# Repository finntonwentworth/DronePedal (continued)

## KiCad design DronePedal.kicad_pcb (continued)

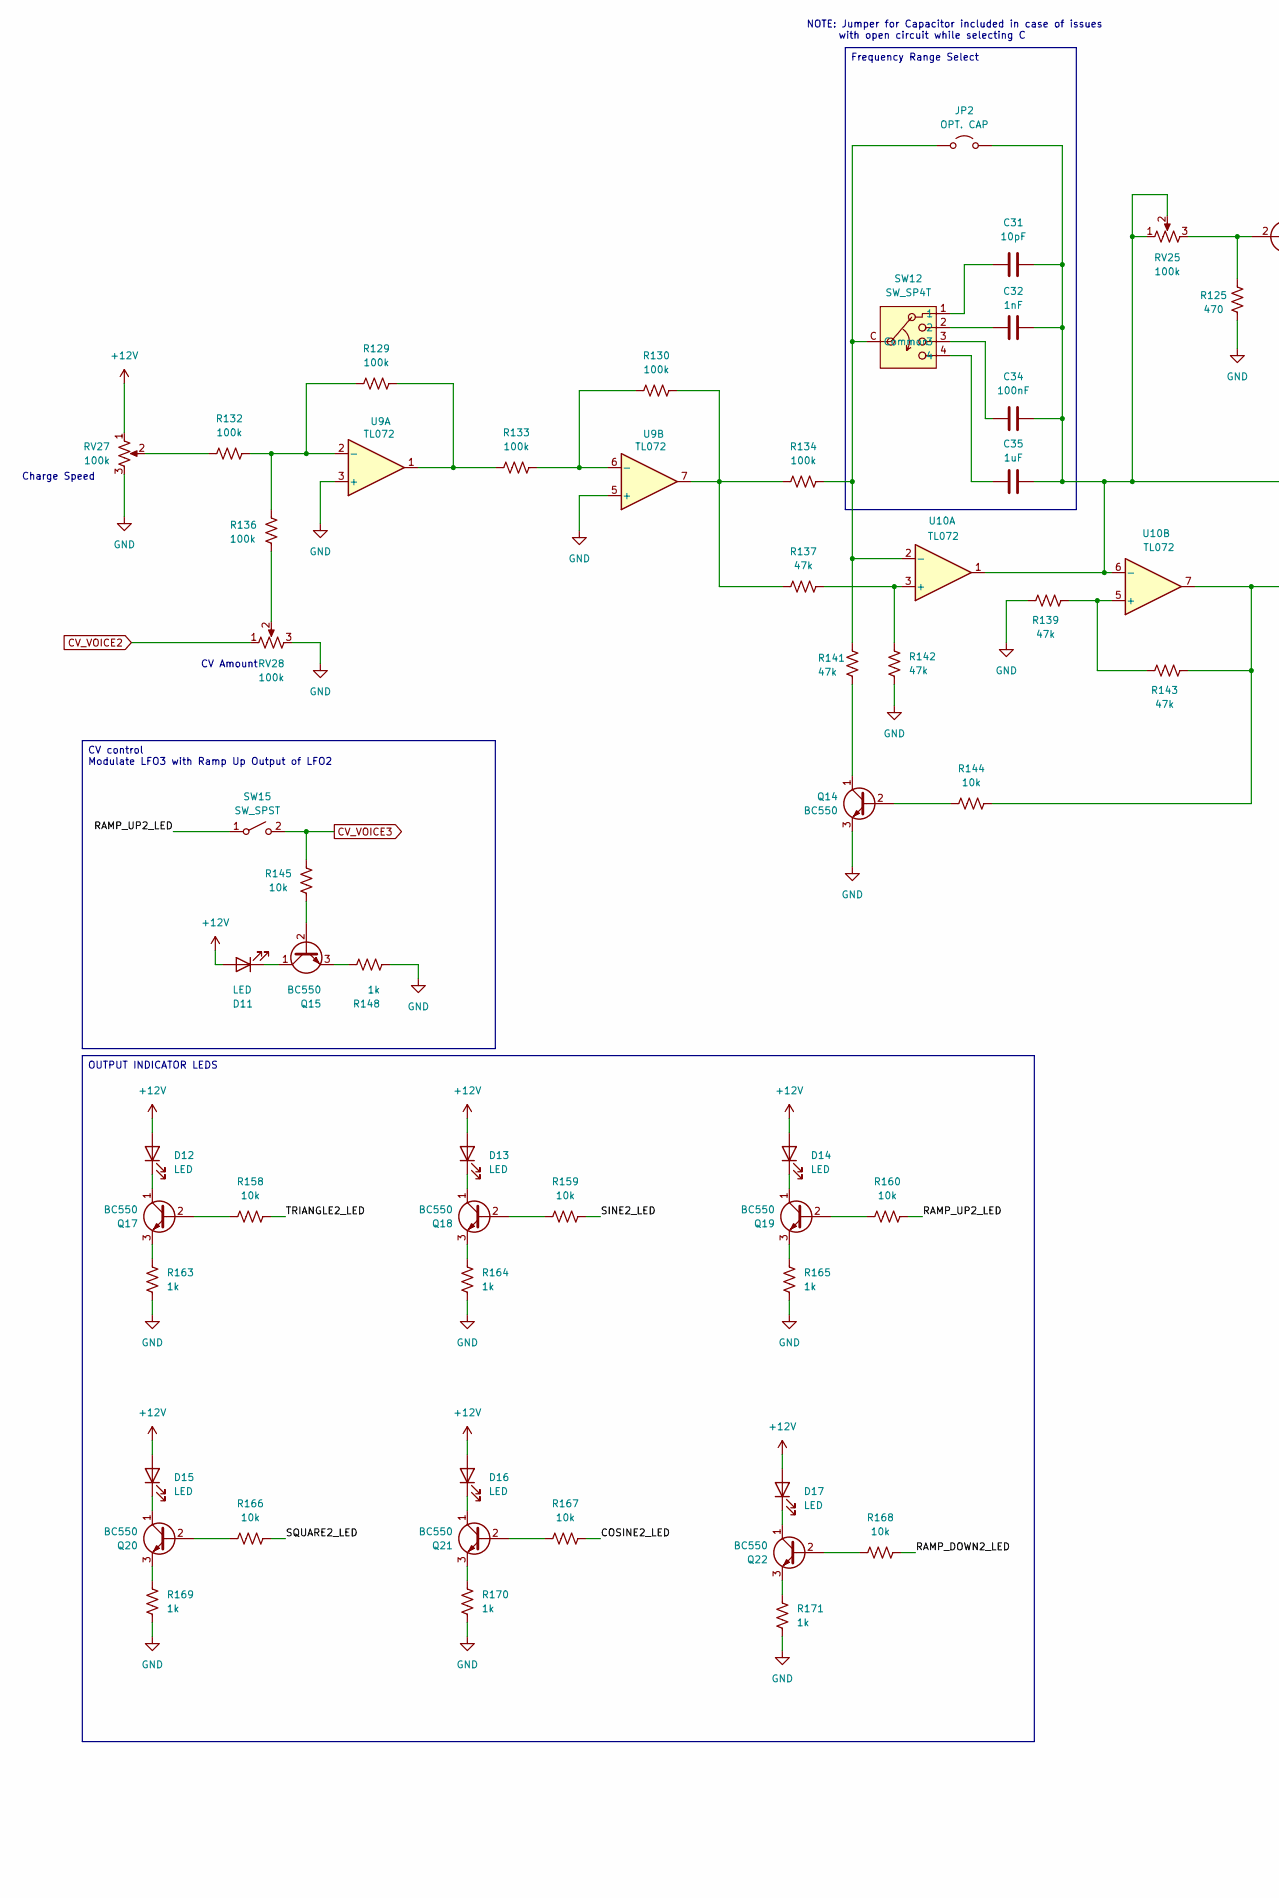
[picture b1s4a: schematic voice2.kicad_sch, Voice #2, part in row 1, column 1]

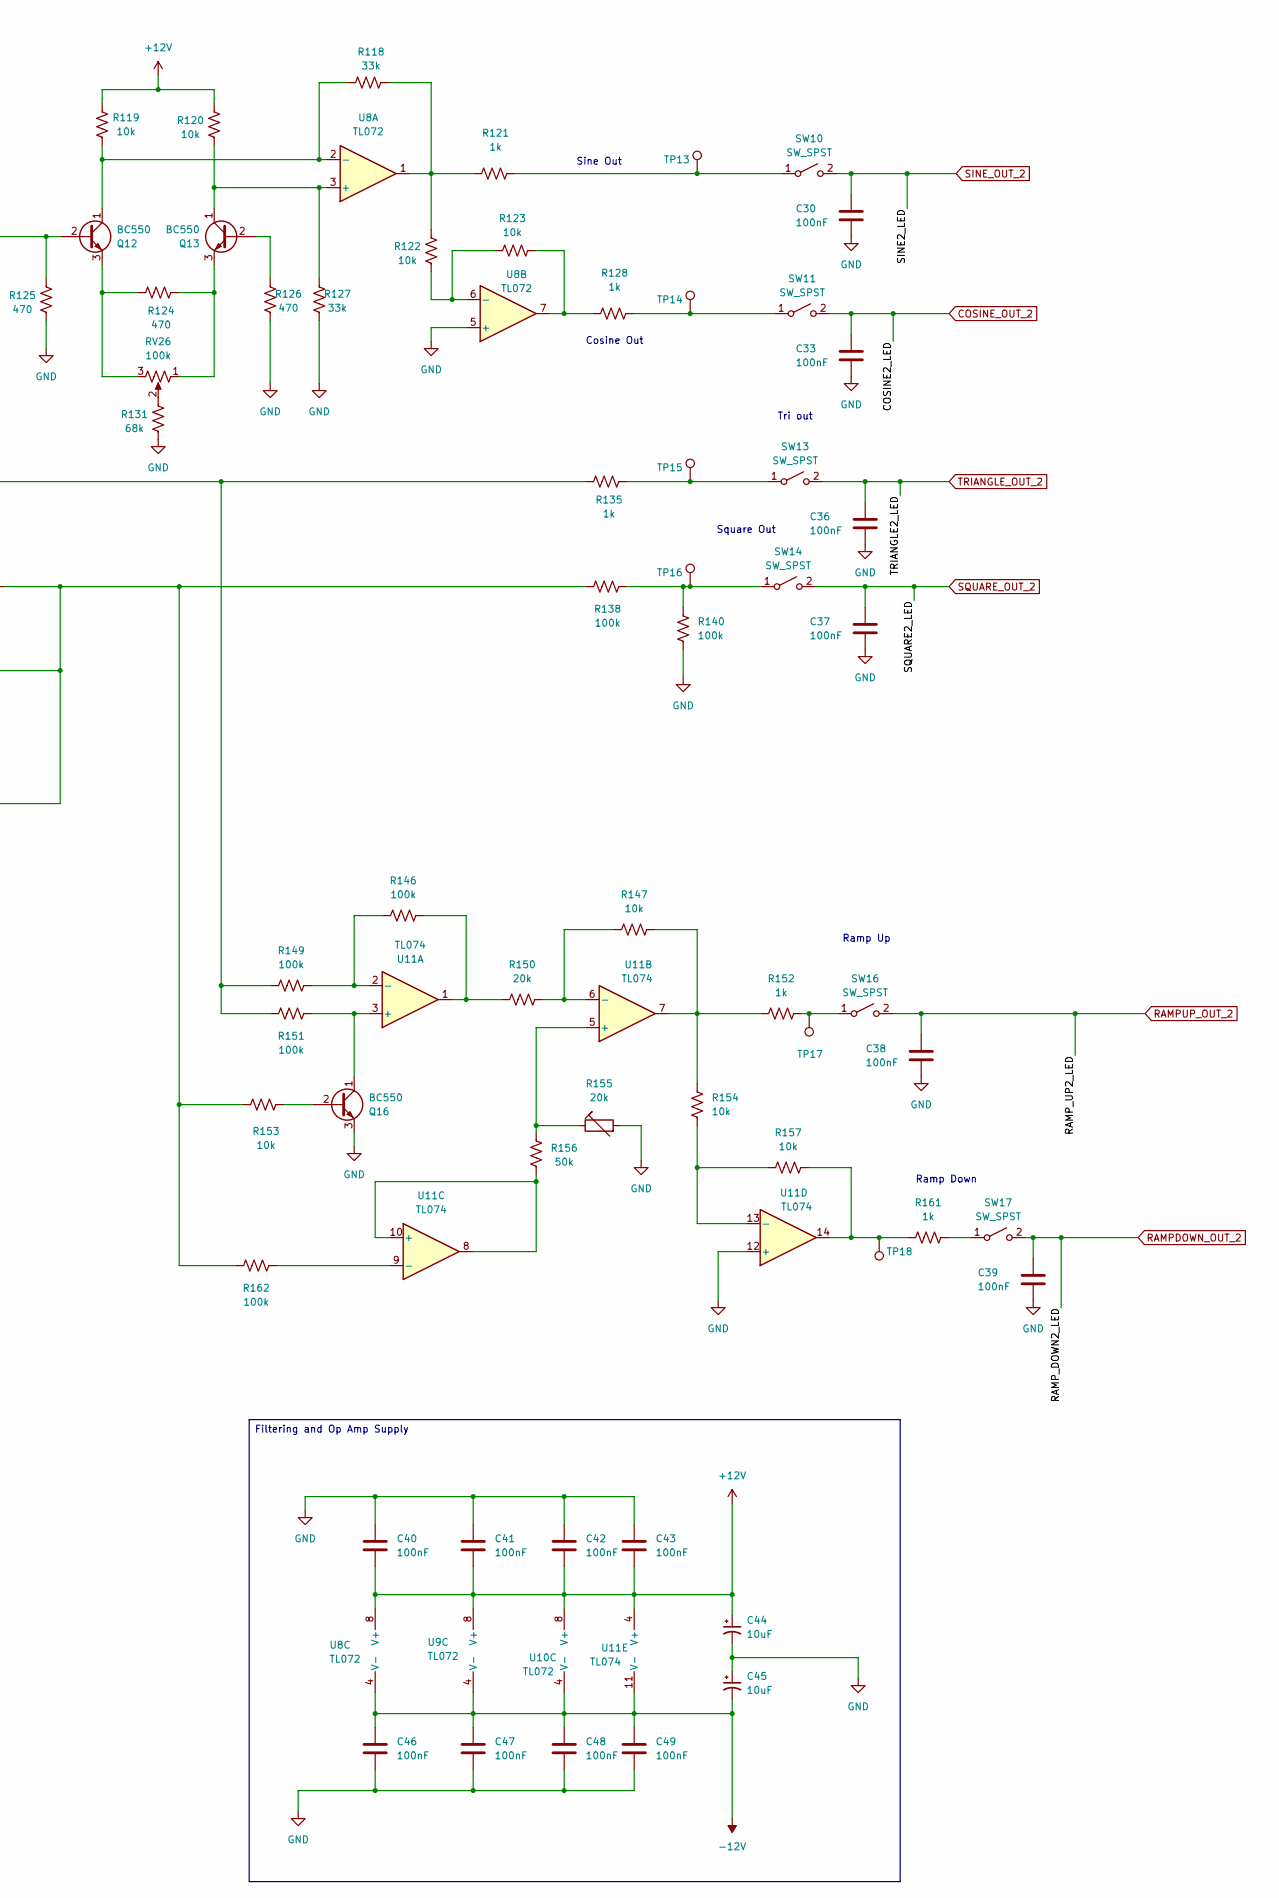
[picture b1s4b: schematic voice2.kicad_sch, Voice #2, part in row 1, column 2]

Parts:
C30, C33, C34, C36, C37, C38, C39, C40, C41, C42, C43, C46, C47, C48, C49: 100nF; C_Disc_D6.0mm_W2.5mm_P5.00mm
C31: 10pF; C_Disc_D4.7mm_W2.5mm_P5.00mm
C32: 1nF; C_Disc_D6.0mm_W2.5mm_P5.00mm
C35: 1uF; C_Disc_D5.0mm_W2.5mm_P2.50mm
C44, C45: 10uF; C_Disc_D6.0mm_W2.5mm_P5.00mm
D11, D12, D13, D14, D15, D16, D17: LED; LED_D1.8mm_W3.3mm_H2.4mm
JP2: OPT. CAP; C_Disc_D5.0mm_W2.5mm_P2.50mm
Q12, Q13, Q14, Q15, Q16, Q17, Q18, Q19, Q20, Q21, Q22: BC550; TO-92_Inline
R118, R127: 33k; R_Axial_DIN0204_L3.6mm_D1.6mm_P5.08mm_Horizontal
R119, R120, R122, R123, R144, R145, R147, R153, R154, R157, R158, R159, R160, R166, R167, R168: 10k; R_Axial_DIN0204_L3.6mm_D1.6mm_P5.08mm_Horizontal
R121, R128, R135, R148, R152, R161, R163, R164, R165, R169, R170, R171: 1k; R_Axial_DIN0204_L3.6mm_D1.6mm_P5.08mm_Horizontal
R124, R125, R126: 470; R_Axial_DIN0204_L3.6mm_D1.6mm_P5.08mm_Horizontal
R129, R130, R132, R133, R134, R136, R138, R140, R146, R149, R151, R162: 100k; R_Axial_DIN0207_L6.3mm_D2.5mm_P10.16mm_Horizontal
R131: 68k; R_Axial_DIN0204_L3.6mm_D1.6mm_P5.08mm_Horizontal
R137, R139, R141, R142, R143: 47k; R_Axial_DIN0204_L3.6mm_D1.6mm_P5.08mm_Horizontal
R150: 20k; R_Axial_DIN0204_L3.6mm_D1.6mm_P5.08mm_Horizontal
R155: 20k; PinHeader_1x03_P2.54mm_Vertical
R156: 50k; R_Axial_DIN0207_L6.3mm_D2.5mm_P7.62mm_Horizontal
RV25, RV26, RV27, RV28: 100k; PinHeader_1x03_P2.54mm_Vertical
SW10, SW11, SW13, SW14, SW15, SW16, SW17: SW_SPST; PinHeader_1x02_P2.54mm_Vertical
SW12: SW_SP4T; PinHeader_1x05_P2.54mm_Vertical
TP13, TP14, TP15, TP16, TP17, TP18: TestPoint_Pad_D1.0mm
U8, U9, U10: TL072; DIP-8_W7.62mm
U11: TL074; DIP-14_W7.62mm

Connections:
+12V: C40.2, C41.2, C42.2, C43.2, C44.1, D11.2 (A), D12.2 (A), D13.2 (A), D14.2 (A), D15.2 (A), D16.2 (A), D17.2 (A), R119.1, R120.1, RV27.1, U8.8 (V+), U9.8 (V+), U10.8 (V+), U11.4 (V+); also elsewhere on the board
-12V: C45.2, C46.1, C47.1, C48.1, C49.1, U8.4 (V-), U9.4 (V-), U10.4 (V-), U11.11 (V-); also elsewhere on the board
COSINE_OUT_2: C33.1, R167.2, SW11.2 (B); also elsewhere on the board
CV_VOICE2: RV28.1; also elsewhere on the board
CV_VOICE3: R145.2, SW15.2 (B); also elsewhere on the board
GND: C30.2, C33.2, C36.2, C37.2, C38.2, C39.2, C40.1, C41.1, C42.1, C43.1, C44.2, C45.1, C46.2, C47.2, C48.2, C49.2, Q14.3 (E), Q16.3 (E), R125.2, R126.1, R127.1, R131.2, R139.2, R140.1, R142.1, R148.1, R155.2, R163.1, R164.1, R165.1, R169.1, R170.1, R171.1, RV27.3, RV28.3, U8.5 (+), U9.3 (+), U9.5 (+), U11.12 (+); also elsewhere on the board
unnamed: C31.1, SW12.1
unnamed: C32.2, SW12.2
unnamed: C34.2, SW12.3
unnamed: C35.2, SW12.4
unnamed: D11.1 (K), Q15.1 (C)
unnamed: D12.1 (K), Q17.1 (C)
unnamed: D13.1 (K), Q18.1 (C)
unnamed: D14.1 (K), Q19.1 (C)
unnamed: D15.1 (K), Q20.1 (C)
unnamed: D16.1 (K), Q21.1 (C)
unnamed: D17.1 (K), Q22.1 (C)
unnamed: JP2.1 (A), R134.2, R141.2, SW12.C (Common), U10.2 (-)
unnamed: C31.2, C32.1, C34.1, C35.1, JP2.2 (B), R135.2, R149.1, R151.1, RV25.1, RV25.2, U10.1, U10.6 (-)
unnamed: Q12.2 (B), R125.1, RV25.3
unnamed: Q12.1 (C), R118.2, R119.2, U8.2 (-)
unnamed: Q12.3 (E), R124.1, RV26.3
unnamed: Q13.2 (B), R126.2
unnamed: Q13.1 (C), R120.2, R127.2, U8.3 (+)
unnamed: Q13.3 (E), R124.2, RV26.1
unnamed: Q14.2 (B), R144.1
unnamed: Q14.1 (C), R141.1
unnamed: Q15.2 (B), R145.1
unnamed: Q15.3 (E), R148.2
unnamed: Q16.2 (B), R153.2
unnamed: Q16.1 (C), R151.2, U11.3 (+)
unnamed: Q17.2 (B), R158.1
unnamed: Q17.3 (E), R163.2
unnamed: Q18.2 (B), R159.1
unnamed: Q18.3 (E), R164.2
unnamed: Q19.2 (B), R160.1
unnamed: Q19.3 (E), R165.2
unnamed: Q20.2 (B), R166.1
unnamed: Q20.3 (E), R169.2
unnamed: Q21.2 (B), R167.1
unnamed: Q21.3 (E), R170.2
unnamed: Q22.2 (B), R168.1
unnamed: Q22.3 (E), R171.2
unnamed: R118.1, R121.2, R122.1, U8.1
unnamed: R123.1, R128.2, U8.7
unnamed: R129.2, R133.1, U9.1
unnamed: R130.2, R134.1, R137.1, U9.7
unnamed: R131.1, RV26.2
unnamed: R132.1, RV27.2
unnamed: R136.1, RV28.2
unnamed: R138.1, R143.1, R144.2, R153.1, R162.1, U10.7
unnamed: R146.2, R150.1, U11.1
unnamed: R147.2, R152.1, R154.2, U11.7
unnamed: R157.1, R161.2, TP18.1, U11.14
unnamed: R121.1, SW10.1 (A), TP13.1
unnamed: R128.1, SW11.1 (A), TP14.1
unnamed: R135.1, SW13.1 (A), TP15.1
unnamed: R138.2, R140.2, SW14.1 (A), TP16.1
unnamed: R152.2, SW16.1 (A), TP17.1
unnamed: R161.1, SW17.1 (A)
unnamed: R122.2, R123.2, U8.6 (-)
unnamed: R129.1, R132.2, R136.2, U9.2 (-)
unnamed: R130.1, R133.2, U9.6 (-)
unnamed: R137.2, R142.2, U10.3 (+)
unnamed: R139.1, R143.2, U10.5 (+)
unnamed: R146.1, R149.2, U11.2 (-)
unnamed: R155.1, R156.2, U11.5 (+)
unnamed: R147.1, R150.2, U11.6 (-)
unnamed: R156.1, U11.8, U11.10 (+)
unnamed: R162.2, U11.9 (-)
unnamed: R154.1, R157.2, U11.13 (-)
RAMPDOWN_OUT_2: C39.1, R168.2, SW17.2 (B); also elsewhere on the board
RAMPUP_OUT_2: C38.1, R160.2, SW15.1 (A), SW16.2 (B); also elsewhere on the board
SINE_OUT_2: C30.1, R159.2, SW10.2 (B); also elsewhere on the board
SQUARE_OUT_2: C37.1, R166.2, SW14.2 (B); also elsewhere on the board
TRIANGLE_OUT_2: C36.1, R158.2, SW13.2 (B); also elsewhere on the board

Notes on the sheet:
NOTE: Jumper for Capacitor included in case of issues with open circuit while selecting C
Charge Speed
CV Amount
Square Out
Sine Out
Tri out
Cosine Out
Ramp Up
Ramp Down
Frequency Range Select
OUTPUT INDICATOR LEDS
CV control Modulate LFO3 with Ramp Up Output of LFO2
Filtering and Op Amp Supply

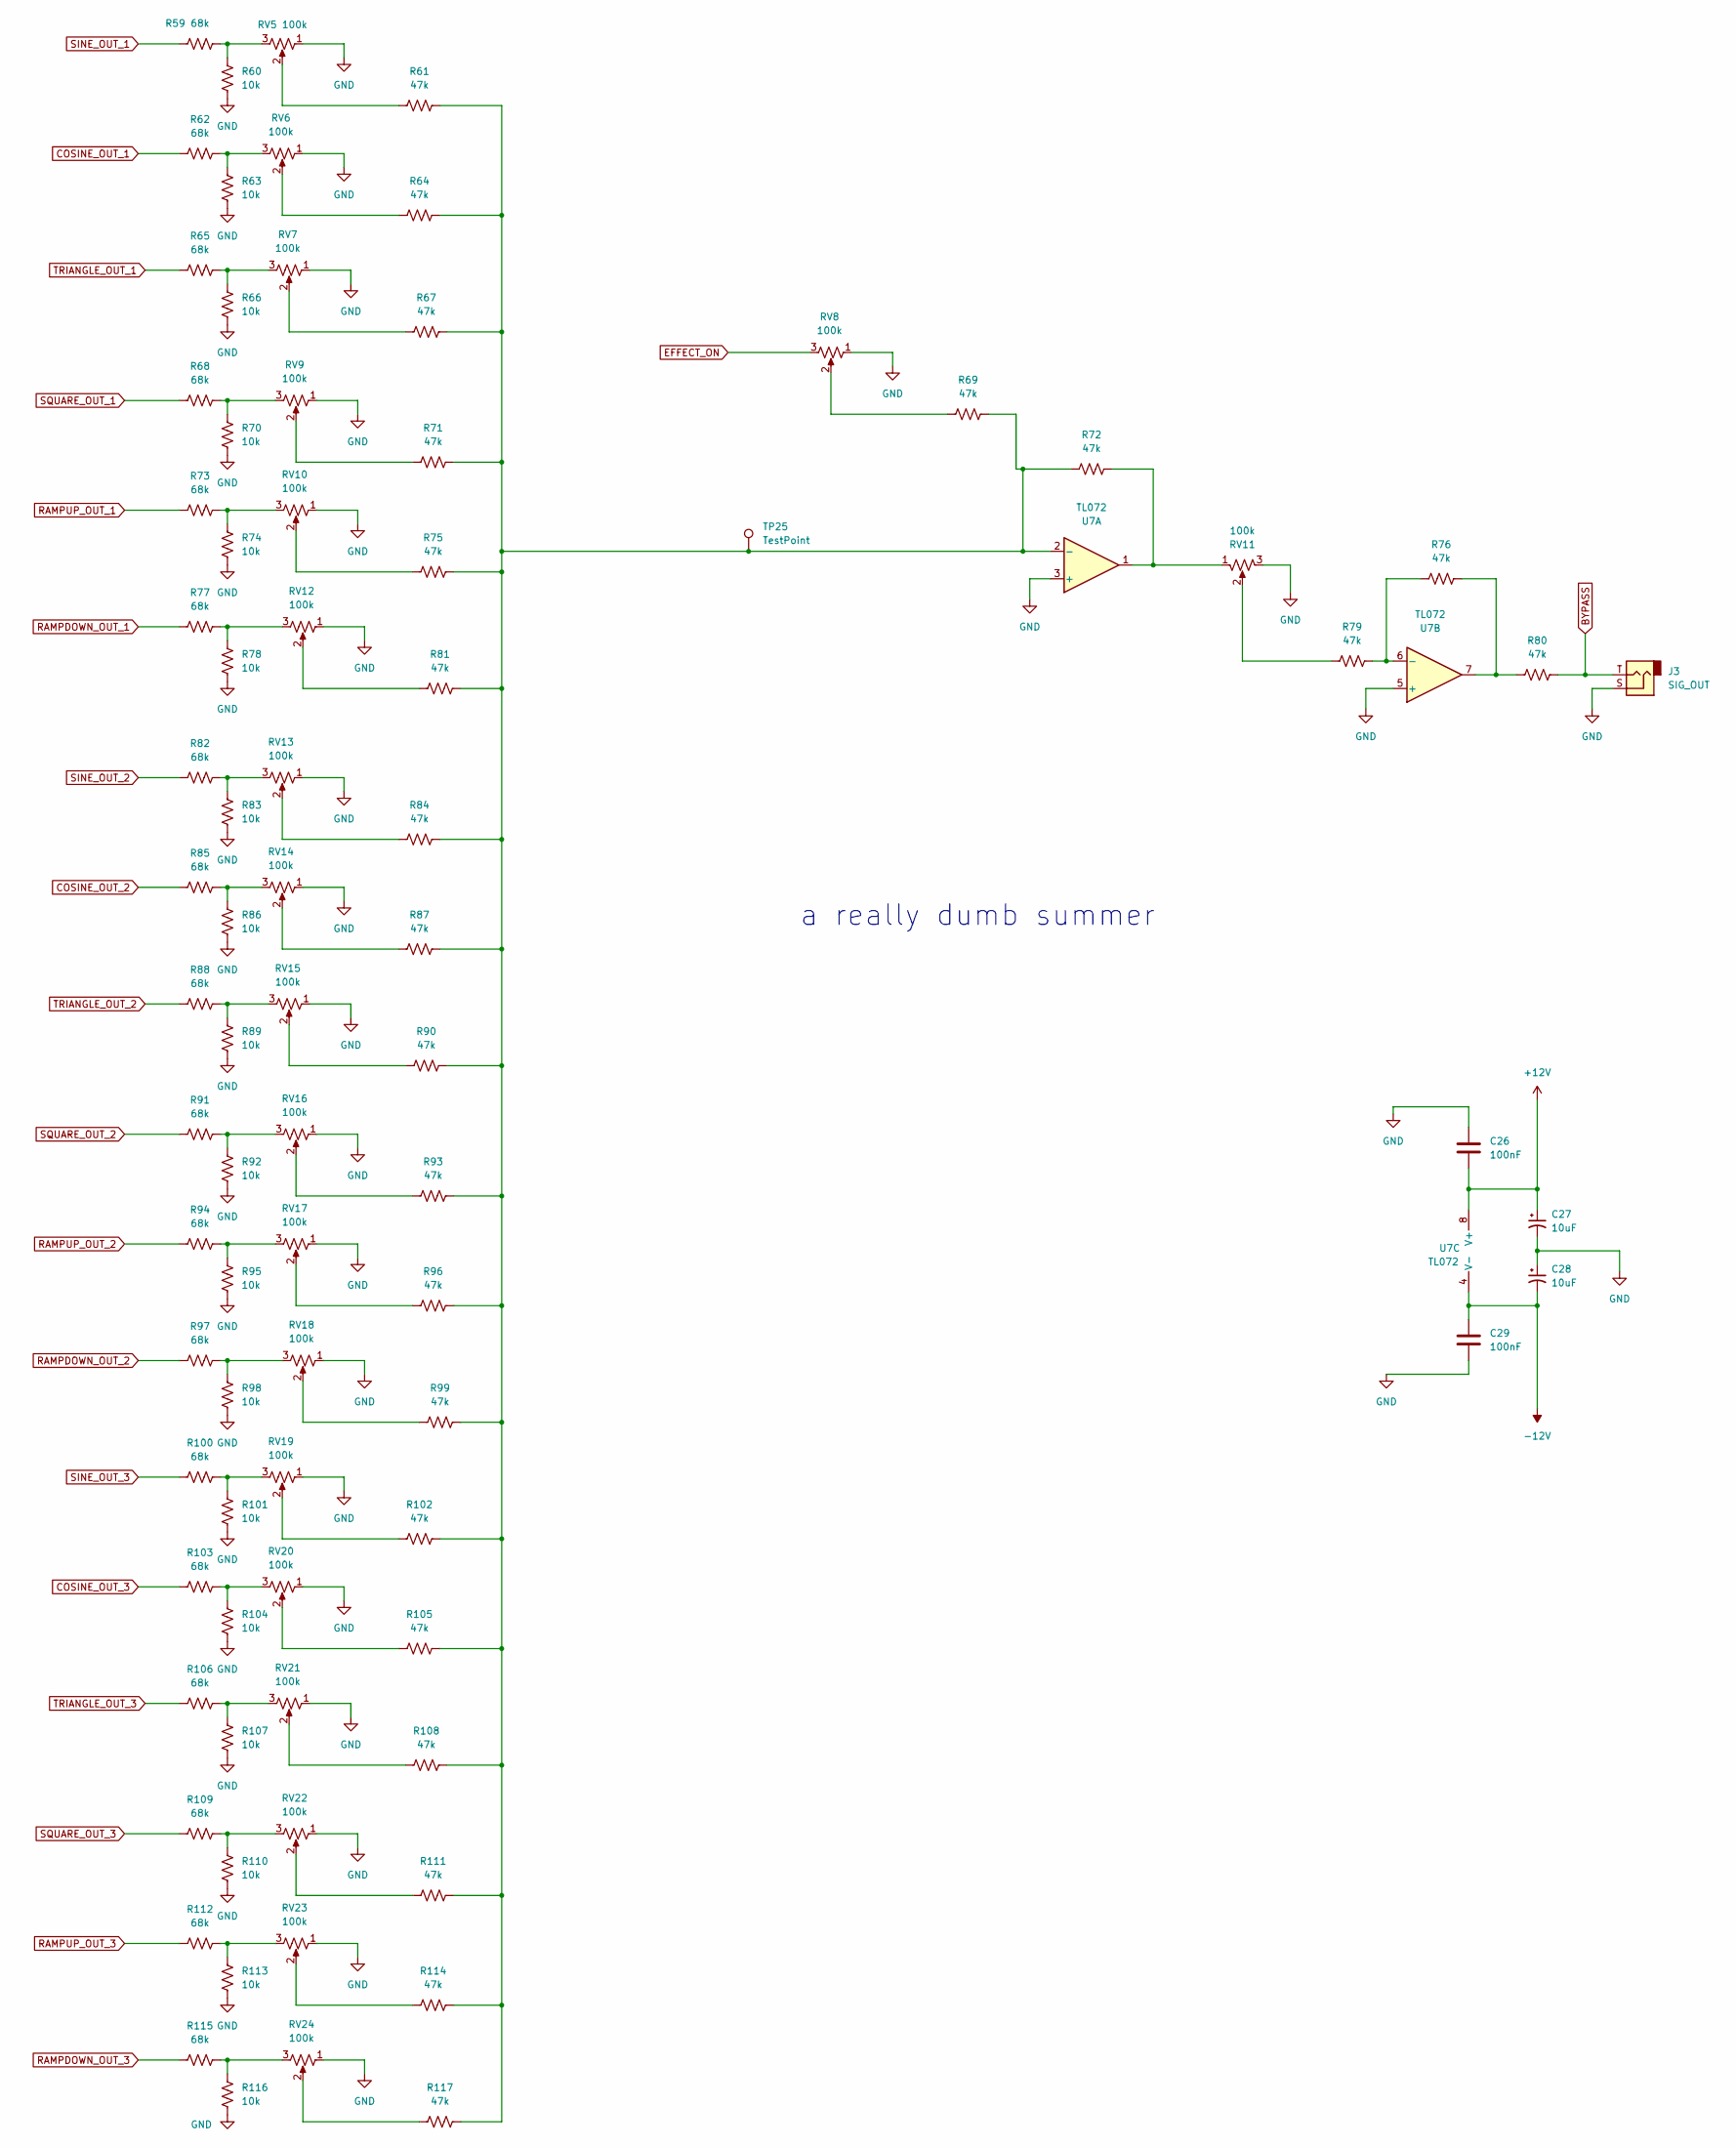
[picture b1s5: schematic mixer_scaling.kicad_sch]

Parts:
C26, C29: 100nF; C_Disc_D6.0mm_W2.5mm_P5.00mm
C27, C28: 10uF; C_Disc_D6.0mm_W2.5mm_P5.00mm
J3: SIG_OUT; PinHeader_1x02_P2.54mm_Vertical
R59, R62, R65, R68, R73, R77, R82, R85, R88, R91, R94, R97, R100, R103, R106, R109, R112, R115: 68k; R_Axial_DIN0204_L3.6mm_D1.6mm_P5.08mm_Horizontal
R60, R63, R66, R70, R74, R78, R83, R86, R89, R92, R95, R98, R101, R104, R107, R110, R113, R116: 10k; R_Axial_DIN0204_L3.6mm_D1.6mm_P5.08mm_Horizontal
R61, R64, R67, R69, R71, R72, R75, R76, R79, R80, R81, R84, R87, R90, R93, R96, R99, R102, R105, R108, R111, R114, R117: 47k; R_Axial_DIN0204_L3.6mm_D1.6mm_P5.08mm_Horizontal
RV5, RV6, RV7, RV8, RV9, RV10, RV11, RV12, RV13, RV14, RV15, RV16, RV17, RV18, RV19, RV20, RV21, RV22, RV23, RV24: 100k; PinHeader_1x03_P2.54mm_Vertical
TP25: TestPoint
U7: TL072; DIP-8_W7.62mm

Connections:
+12V: C26.2, C27.1, U7.8 (V+); also elsewhere on the board
-12V: C28.2, C29.1, U7.4 (V-); also elsewhere on the board
BYPASS: J3.T, R80.2; also elsewhere on the board
COSINE_OUT_1: R62.1; also elsewhere on the board
COSINE_OUT_2: R85.1; also elsewhere on the board
COSINE_OUT_3: R103.1; also elsewhere on the board
EFFECT_ON: RV8.3; also elsewhere on the board
GND: C26.1, C27.2, C28.1, C29.2, J3.S, R60.1, R63.1, R66.1, R70.1, R74.1, R78.1, R83.1, R86.1, R89.1, R92.1, R95.1, R98.1, R101.1, R104.1, R107.1, R110.1, R113.1, R116.1, RV5.1, RV6.1, RV7.1, RV8.1, RV9.1, RV10.1, RV11.3, RV12.1, RV13.1, RV14.1, RV15.1, RV16.1, RV17.1, RV18.1, RV19.1, RV20.1, RV21.1, RV22.1, RV23.1, RV24.1, U7.3 (+), U7.5 (+); also elsewhere on the board
unnamed: R59.2, R60.2, RV5.3
unnamed: R61.1, RV5.2
unnamed: R62.2, R63.2, RV6.3
unnamed: R64.1, RV6.2
unnamed: R65.2, R66.2, RV7.3
unnamed: R67.1, RV7.2
unnamed: R68.2, R70.2, RV9.3
unnamed: R69.1, RV8.2
unnamed: R71.1, RV9.2
unnamed: R72.2, RV11.1, U7.1
unnamed: R73.2, R74.2, RV10.3
unnamed: R75.1, RV10.2
unnamed: R76.2, R80.1, U7.7
unnamed: R77.2, R78.2, RV12.3
unnamed: R79.1, RV11.2
unnamed: R81.1, RV12.2
unnamed: R82.2, R83.2, RV13.3
unnamed: R84.1, RV13.2
unnamed: R85.2, R86.2, RV14.3
unnamed: R87.1, RV14.2
unnamed: R88.2, R89.2, RV15.3
unnamed: R90.1, RV15.2
unnamed: R91.2, R92.2, RV16.3
unnamed: R93.1, RV16.2
unnamed: R94.2, R95.2, RV17.3
unnamed: R96.1, RV17.2
unnamed: R97.2, R98.2, RV18.3
unnamed: R99.1, RV18.2
unnamed: R100.2, R101.2, RV19.3
unnamed: R102.1, RV19.2
unnamed: R103.2, R104.2, RV20.3
unnamed: R105.1, RV20.2
unnamed: R106.2, R107.2, RV21.3
unnamed: R108.1, RV21.2
unnamed: R109.2, R110.2, RV22.3
unnamed: R111.1, RV22.2
unnamed: R112.2, R113.2, RV23.3
unnamed: R114.1, RV23.2
unnamed: R115.2, R116.2, RV24.3
unnamed: R117.1, RV24.2
unnamed: R61.2, R64.2, R67.2, R69.2, R71.2, R72.1, R75.2, R81.2, R84.2, R87.2, R90.2, R93.2, R96.2, R99.2, R102.2, R105.2, R108.2, R111.2, R114.2, R117.2, TP25.1, U7.2 (-)
unnamed: R76.1, R79.2, U7.6 (-)
RAMPDOWN_OUT_1: R77.1; also elsewhere on the board
RAMPDOWN_OUT_2: R97.1; also elsewhere on the board
RAMPDOWN_OUT_3: R115.1; also elsewhere on the board
RAMPUP_OUT_1: R73.1; also elsewhere on the board
RAMPUP_OUT_2: R94.1; also elsewhere on the board
RAMPUP_OUT_3: R112.1; also elsewhere on the board
SINE_OUT_1: R59.1; also elsewhere on the board
SINE_OUT_2: R82.1; also elsewhere on the board
SINE_OUT_3: R100.1; also elsewhere on the board
SQUARE_OUT_1: R68.1; also elsewhere on the board
SQUARE_OUT_2: R91.1; also elsewhere on the board
SQUARE_OUT_3: R109.1; also elsewhere on the board
TRIANGLE_OUT_1: R65.1; also elsewhere on the board
TRIANGLE_OUT_2: R88.1; also elsewhere on the board
TRIANGLE_OUT_3: R106.1; also elsewhere on the board

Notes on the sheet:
a really dumb summer

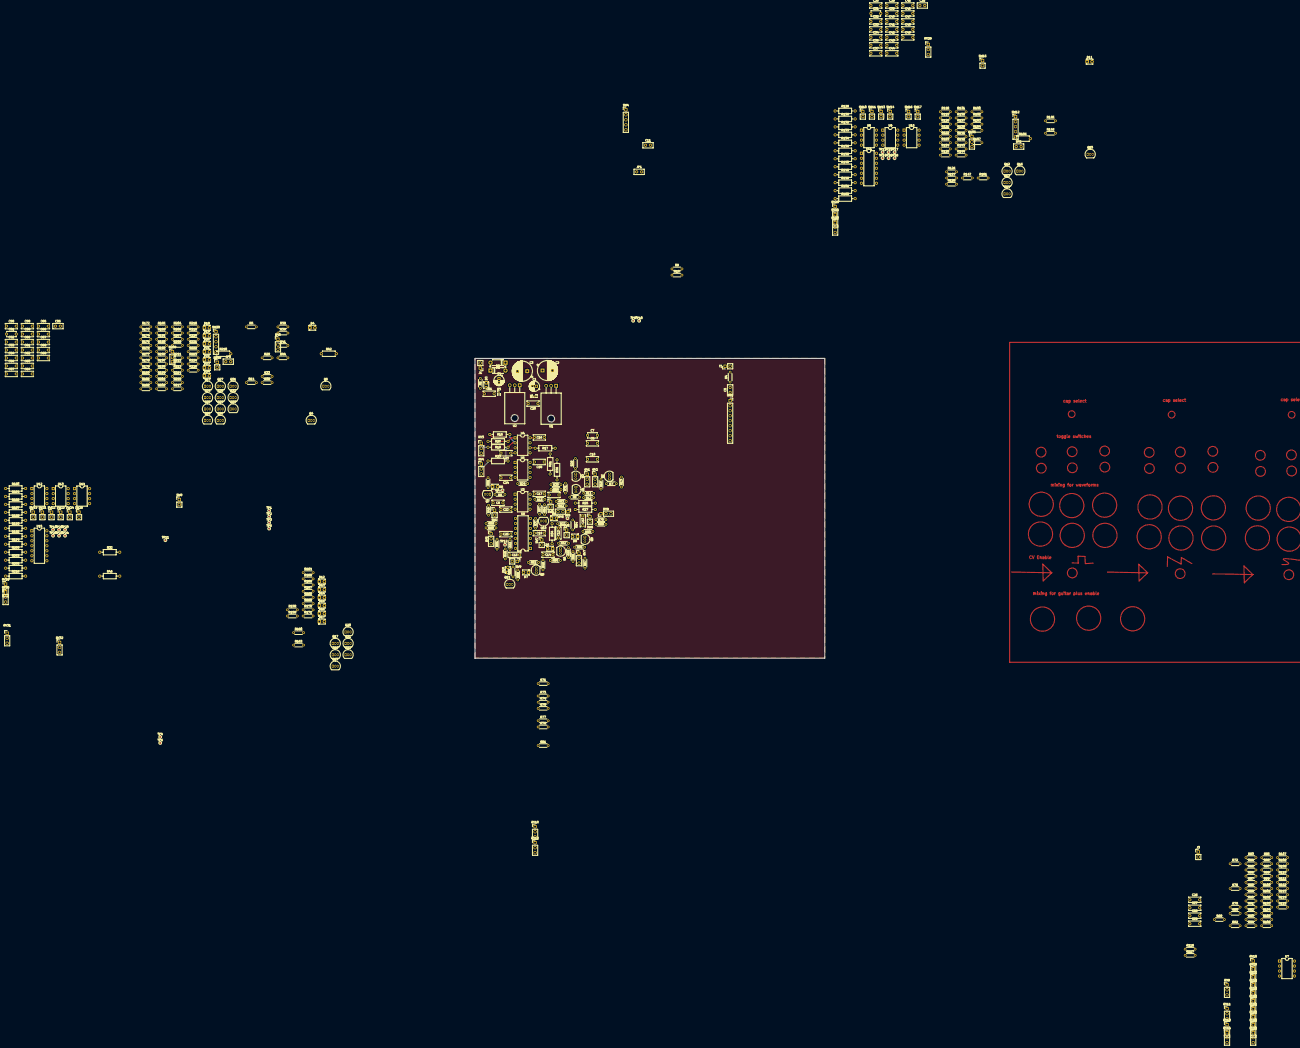
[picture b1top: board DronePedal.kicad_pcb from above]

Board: 2 copper layers, 177.8 x 152.4 mm, 453 parts (0 on the bottom side), 272 nets.

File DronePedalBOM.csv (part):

"Reference","Value","Datasheet","Footprint","Qty","DNP","Link"
"C1,C4,C11,C35,C55","1uF","https://product.tdk.com/en/system/files/dam/doc/product/capa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,https://www.we-online.com/components/products/datasheet/8600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","Capacitor_THT:CP_Radial_D5.0mm_P2.00mm,Capacitor_THT:C_Disc_D5.0mm_W2.5mm_P2.50mm","5","","https://www.digikey.com/en/products/detail/tdk-corporation/F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,https://www.digikey.com/en/products/detail/w%C3%BCrth-elektr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"
"C2,C3","470uF","https://www.nichicon.co.jp/english/series_items/catalog_pdf/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","Capacitor_THT:CP_Radial_D10.0mm_P5.00mm","2","","https://www.digikey.com/en/products/detail/nichicon/UHE1C471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"
"C5","470nF","https://product.tdk.com/en/system/files/dam/doc/product/capa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","Capacitor_THT:C_Disc_D5.0mm_W2.5mm_P2.50mm","1","","https://www.digikey.com/en/products/detail/tdk-corporation/F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"
"C6,C9,C10,C12,C13,C14,C15,C16,C17,C18,C19,C22,C23,C24,C25,C26,C29,C30,C33,C34,C36,C37,C38,C39,C40,C41,C42,C43,C46,C47,C48,C49,C50,C53,C54,C56,C57,C58,C59,C60,C61,C62,C63,C66,C67,C68,C69","100nF","https://content.kemet.com/datasheets/KEM_C1050_GOLDMAX_X7R.pdf","Capacitor_THT:C_Disc_D6.0mm_W2.5mm_P5.00mm","47","","https://www.digikey.com/en/products/detail/kemet/C320C104K5R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"
"C7,C31,C51","10pF","https://product.tdk.com/en/system/files/dam/doc/product/capa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","Capacitor_THT:C_Disc_D4.7mm_W2.5mm_P5.00mm","3","","https://www.digikey.com/en/products/detail/tdk-corporation/F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"
"C8,C32,C52","1nF","https://www.vishay.com/docs/22202/wyo.pdf","Capacitor_THT:C_Disc_D6.0mm_W2.5mm_P5.00mm","3","","https://www.digikey.com/en/products/detail/vishay-beyschlag-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"
"C20,C21,C27,C28,C44,C45,C64,C65","10uF","https://search.murata.co.jp/Ceramy/image/img/A01X/G101/ENG/R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","Capacitor_THT:C_Disc_D6.0mm_W2.5mm_P5.00mm","8","","https://www.digikey.com/en/products/detail/murata-electronic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"
"D1,D2","1N4001","~","Diode_THT:D_DO-41_SOD81_P7.62mm_Horizontal","2","","https://www.digikey.com/en/products/detail/onsemi/1N4001G/1485468"
"D3,D4,D5,D6,D7,D8,D9,D10,D11,D12,D13,D14,D15,D16,D17,D18,D19,D20,D21,D22,D23,D24","LED","~","LED_THT:LED_D1.8mm_W3.3mm_H2.4mm","22","",""
"J1","Barrel_Jack","https://downloads.lumberg.com/datenblaetter/en/1614_23.pdf","Connector_PinHeader_2.54mm:PinHeader_1x02_P2.54mm_Vertical","1","","https://www.digikey.com/en/products/detail/lumberg-inc/1614-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"
"J2","Guitar Jack","~","Connector_PinHeader_2.54mm:PinHeader_1x02_P2.54mm_Vertical","1","","https://www.digikey.com/en/products/detail/switchcraft-inc/L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"
"J3","SIG_OUT","~","Connector_PinHeader_2.54mm:PinHeader_1x02_P2.54mm_Vertical","1","","https://www.digikey.com/en/products/detail/switchcraft-inc/L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"
"JP1,JP2,JP3","OPT. CAP","~","Capacitor_THT:C_Disc_D5.0mm_W2.5mm_P2.50mm","3","",""
"Q1,Q2,Q3,Q4,Q5,Q6,Q7,Q8,Q9,Q10,Q11,Q12,Q13,Q14,Q15,Q16,Q17,Q18,Q19,Q20,Q21,Q22,Q23,Q24,Q25,Q26,Q27,Q28,Q29,Q30,Q31,Q32,Q33","BC550","https://www.onsemi.com/pub/Collateral/BC550-D.pdf","Package_TO_SOT_THT:TO-92_Inline","33","","https://www.mouser.com/ProductDetail/onsemi-Fairchild/BC550C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"
"R1,R3","0 ohm","~","Connector_PinHeader_1.00mm:PinHeader_1x02_P1.00mm_Vertical","2","",""
"R2","4.7k","https://www.seielect.com/catalog/sei-cf_cfm.pdf","Resistor_THT:R_Axial_DIN0204_L3.6mm_D1.6mm_P5.08mm_Horizontal","1","","https://www.digikey.com/en/products/detail/stackpole-electro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"
"R4,R8,R15,R22,R37,R44,R45,R50,R51,R52,R56,R57,R58,R121,R128,R135,R148,R152,R161,R163,R164,R165,R169,R170,R171,R175,R182,R189,R202,R206,R215,R217,R218,R219,R223,R224,R225","1k","https://www.seielect.com/catalog/sei-cf_cfm.pdf","Resistor_THT:R_Axial_DIN0204_L3.6mm_D1.6mm_P5.08mm_Horizontal","37","","https://www.digikey.com/en/products/detail/stackpole-electro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"
"R5,R14,R118,R127,R172,R181","33k","https://www.seielect.com/catalog/sei-cf_cfm.pdf","Resistor_THT:R_Axial_DIN0204_L3.6mm_D1.6mm_P5.08mm_Horizontal","6","","https://www.digikey.com/en/products/detail/stackpole-electro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"
"R6,R7,R9,R10,R31,R33,R38,R39,R41,R43,R47,R48,R49,R53,R54,R55,R60,R63,R66,R70,R74,R78,R83,R86,R89,R92,R95,R98,R101,R104,R107,R110,R113,R116,R119,R120,R122,R123,R144,R145,R147,R153,R154,R157,R158,R159,R160,R166,R167,R168,R173,R174,R176,R177,R198,R199,R201,R207,R208,R211,R212,R213,R214,R220,R221,R222","10k","https://www.seielect.com/catalog/sei-cf_cfm.pdf","Resistor_THT:R_Axial_DIN0204_L3.6mm_D1.6mm_P5.08mm_Horizontal","66","","https://www.digikey.com/en/products/detail/stackpole-electro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"
"R11,R12,R13,R124,R125,R126,R178,R179,R180","470","https://www.seielect.com/catalog/sei-cf_cfm.pdf","Resistor_THT:R_Axial_DIN0204_L3.6mm_D1.6mm_P5.08mm_Horizontal","9",""," https://www.digikey.com/en/products/detail/stackpole-electro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"
"R16,R17,R19,R20,R21,R23,R25,R27,R32,R34,R36,R46,R129,R130,R132,R133,R134,R136,R138,R140,R146,R149,R151,R162,R183,R184,R186,R187,R188,R190,R192,R194,R200,R203,R205,R216,RV1,RV2,RV3,RV4,RV5,RV6,RV7,RV8,RV9,RV10,RV11,RV12,RV13,RV14,RV15,RV16,RV17,RV18,RV19,RV20,RV21,RV22,RV23,RV24,RV25,RV26,RV27,RV28,RV29,RV30,RV31,RV32","100k","https://www.digikey.com/en/products/detail/bourns-inc/3296W-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,https://www.digikey.com/en/products/detail/yageo/MFR50SFTE52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,https://www.mouser.com/datasheet/2/1628/ptn09x-3510641.pdf","Connector_PinHeader_2.54mm:PinHeader_1x03_P2.54mm_Vertical,Resistor_THT:R_Axial_DIN0207_L6.3mm_D2.5mm_P10.16mm_Horizontal","68","","https://www.digikey.com/en/products/detail/bourns-inc/3296W-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,https://www.digikey.com/en/products/detail/yageo/MFP-25BRD52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,https://www.mouser.com/ProductDetail/Same-Sky/PTN091-H100115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,https://www.mouser.com/ProductDetail/Same-Sky/PTN091-H100115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"
"R18,R59,R62,R65,R68,R73,R77,R82,R85,R88,R91,R94,R97,R100,R103,R106,R109,R112,R115,R131,R185","68k","https://www.yageo.com/upload/media/product/app/datasheet/lr/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","Resistor_THT:R_Axial_DIN0204_L3.6mm_D1.6mm_P5.08mm_Horizontal","21","","https://www.digikey.com/en/products/detail/yageo/MFR50SFTE52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"
"R24,R26,R28,R29,R30,R61,R64,R67,R69,R71,R72,R75,R76,R79,R80,R81,R84,R87,R90,R93,R96,R99,R102,R105,R108,R111,R114,R117,R137,R139,R141,R142,R143,R191,R193,R195,R196,R197","47k","https://www.seielect.com/catalog/sei-cf_cfm.pdf","Resistor_THT:R_Axial_DIN0204_L3.6mm_D1.6mm_P5.08mm_Horizontal","38","","https://www.digikey.com/en/products/detail/stackpole-electro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"
"R35,R40,R150,R155,R204,R209","20k","https://www.bourns.com/docs/Product-Datasheets/pv36.pdf,https://www.yageo.com/upload/media/product/app/datasheet/lr/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","Connector_PinHeader_2.54mm:PinHeader_1x03_P2.54mm_Vertical,Resistor_THT:R_Axial_DIN0204_L3.6mm_D1.6mm_P5.08mm_Horizontal","6","","https://www.digikey.com/en/products/detail/bourns-inc/PV36W2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,https://www.digikey.com/en/products/detail/yageo/CFR-50JB-52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"
"R42,R156,R210","50k","https://www.yageo.com/upload/media/product/app/datasheet/lr/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","Resistor_THT:R_Axial_DIN0207_L6.3mm_D2.5mm_P7.62mm_Horizontal","3","","https://www.digikey.com/en/products/detail/yageo/MFP50SBBE52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"
"SW1,TP4,TP6,TP7,TP8,TP9,TP10,TP11,TP12,TP13,TP14,TP15,TP16,TP17,TP18,TP19,TP20,TP21,TP22,TP23,TP24","~","~","Connector_PinSocket_2.54mm:PinSocket_1x09_P2.54mm_Vertical,TestPoint:TestPoint_Pad_D1.0mm","21","","https://lovemyswitches.com/pro-3pdt-latched-foot-switch-sold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"
"SW2,SW3,SW5,SW6,SW7,SW8,SW9,SW10,SW11,SW13,SW14,SW15,SW16,SW17,SW18,SW19,SW21,SW22,SW23,SW24,SW25","SW_SPST","https://www.mouser.com/datasheet/2/4/sw_t3_1a_a_a3_s1_data_s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","Connector_PinHeader_2.54mm:PinHeader_1x02_P2.54mm_Vertical","21","","https://www.mouser.com/ProductDetail/Adam-Tech/SW-T3-1A-A-A3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"
"SW4,SW12,SW20","SW_SP4T","https://www.ckswitches.com/media/1910/rm.pdf","Connector_PinHeader_2.54mm:PinHeader_1x05_P2.54mm_Vertical","3","","https://www.digikey.com/en/products/detail/c-k/RM104772BCB/6052011"
"TP1","+12V","~","TestPoint:TestPoint_Pad_D1.0mm","1","",""
"TP2","-12V","~","TestPoint:TestPoint_Pad_D1.0mm","1","",""
"TP3","GND","~","TestPoint:TestPoint_Pad_D1.0mm","1","",""
"TP5","SIG_IN","~","TestPoint:TestPoint_Pad_D1.0mm","1","",""
"U1","LM7812_TO220","https://www.onsemi.cn/PowerSolutions/document/MC7800-D.PDF","Package_TO_SOT_THT:TO-220-3_Vertical","1","","https://www.digikey.com/en/products/detail/texas-instruments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"
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
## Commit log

2025-03-03 updated gitignore and added README :
2025-03-03 began layout
2025-03-09 more routing progress made
